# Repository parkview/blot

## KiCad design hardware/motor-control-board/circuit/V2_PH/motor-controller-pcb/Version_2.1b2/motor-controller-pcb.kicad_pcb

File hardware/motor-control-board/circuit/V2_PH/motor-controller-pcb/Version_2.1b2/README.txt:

Project Name:  Blot Motor Controller Board
Project date:  2024-01-21

In Shenzhen Leo and I discussed trying out a new version of the Blot controller PCB that uses normal USB-C (non-PD) with a boost circuit to generate the required 9V to run the two stepper motors.  This is my go at it.

Ideally it would all operate from one USB connector if the current is low enough.

PCB Versions:
-------------

Version 2.2b1:
Production:  JLCPCB, 1.6mm, 4 Layer, Green
Date: TBD

* create a dedicated ESP32-C3-WROOM (Mini?) version.  Gives more GPIO and less soldering

Version 2.1b2:
Production:  JLCPCB, 1.6mm, 4 Layer, Green
Date: TBD

* are R9/R17 (motor decay rate) really needed? If Open, it's set to 16uSec Smart Tune
* test out laser cut plastic solder paste stencil
Done: Fix L2 inductor footprint.  Needs to be bigger?
Done: move L2 1mm away from U3
Done: purchase correct 1A polyfuse
Done: purchase backup 1.5A and 2A + 2.5A 0805 polyfuses
Done: was PWM Vref ok to work with?  Yes and cheapest option.
Done: was DAC Vref ok to work with? (increase 3v3 trace width).  Removed. PWM ok.
Done: delete Vref Pots if not needed, otherwise just use 1 Pot to feed both from 3V3
Done: measure power draw: 5V @ 1.1A for two small motors at 9V.
Done: could add a Fuse LED to indicate when it's activated
Done: could add a programmable LED on A3.  It looks to be available
Done: write pinout data on backside of PCB
Done: change R12 to 33K to allow up to 1.4A output at 9V
Done: Add a XC6227 LDO, to power MCU module when running from 2nd USB connector!
Done: add a 22uF to the Servo power line
Done: swap Blot_PCB_Back_v2.1b1out B5819W (1A) dioes for SS24 (2A)
Done: purchase correct 100uF Caps
Done: change M1 from DVDD to 3V3
Done: on backside, label Motor outputs:  A1/A2, B1/B2
Done: add 3V3, both USB 5V inputs as testpoints and label
Done: connect nSleep to 3V3 instead of DVDD
Done: fix R4/R5 labels
No: could add a Fault LED (pullup to 3V3). Space?

Version 2.1b1:
Production:  JLCPCB, 1.6mm, 4 Layer, Green, 5 PCBs
Date: 2024-02-20

* Initial version.

0  IO2 PWM Dac
1  IO3 Motor Enable
2  IO4
3  IO5
4  IO6
5  IO7
6  IO21
7  IO20
8  IO8
9  IO9
10 IO10
11 3V3
12 GND
13 5V

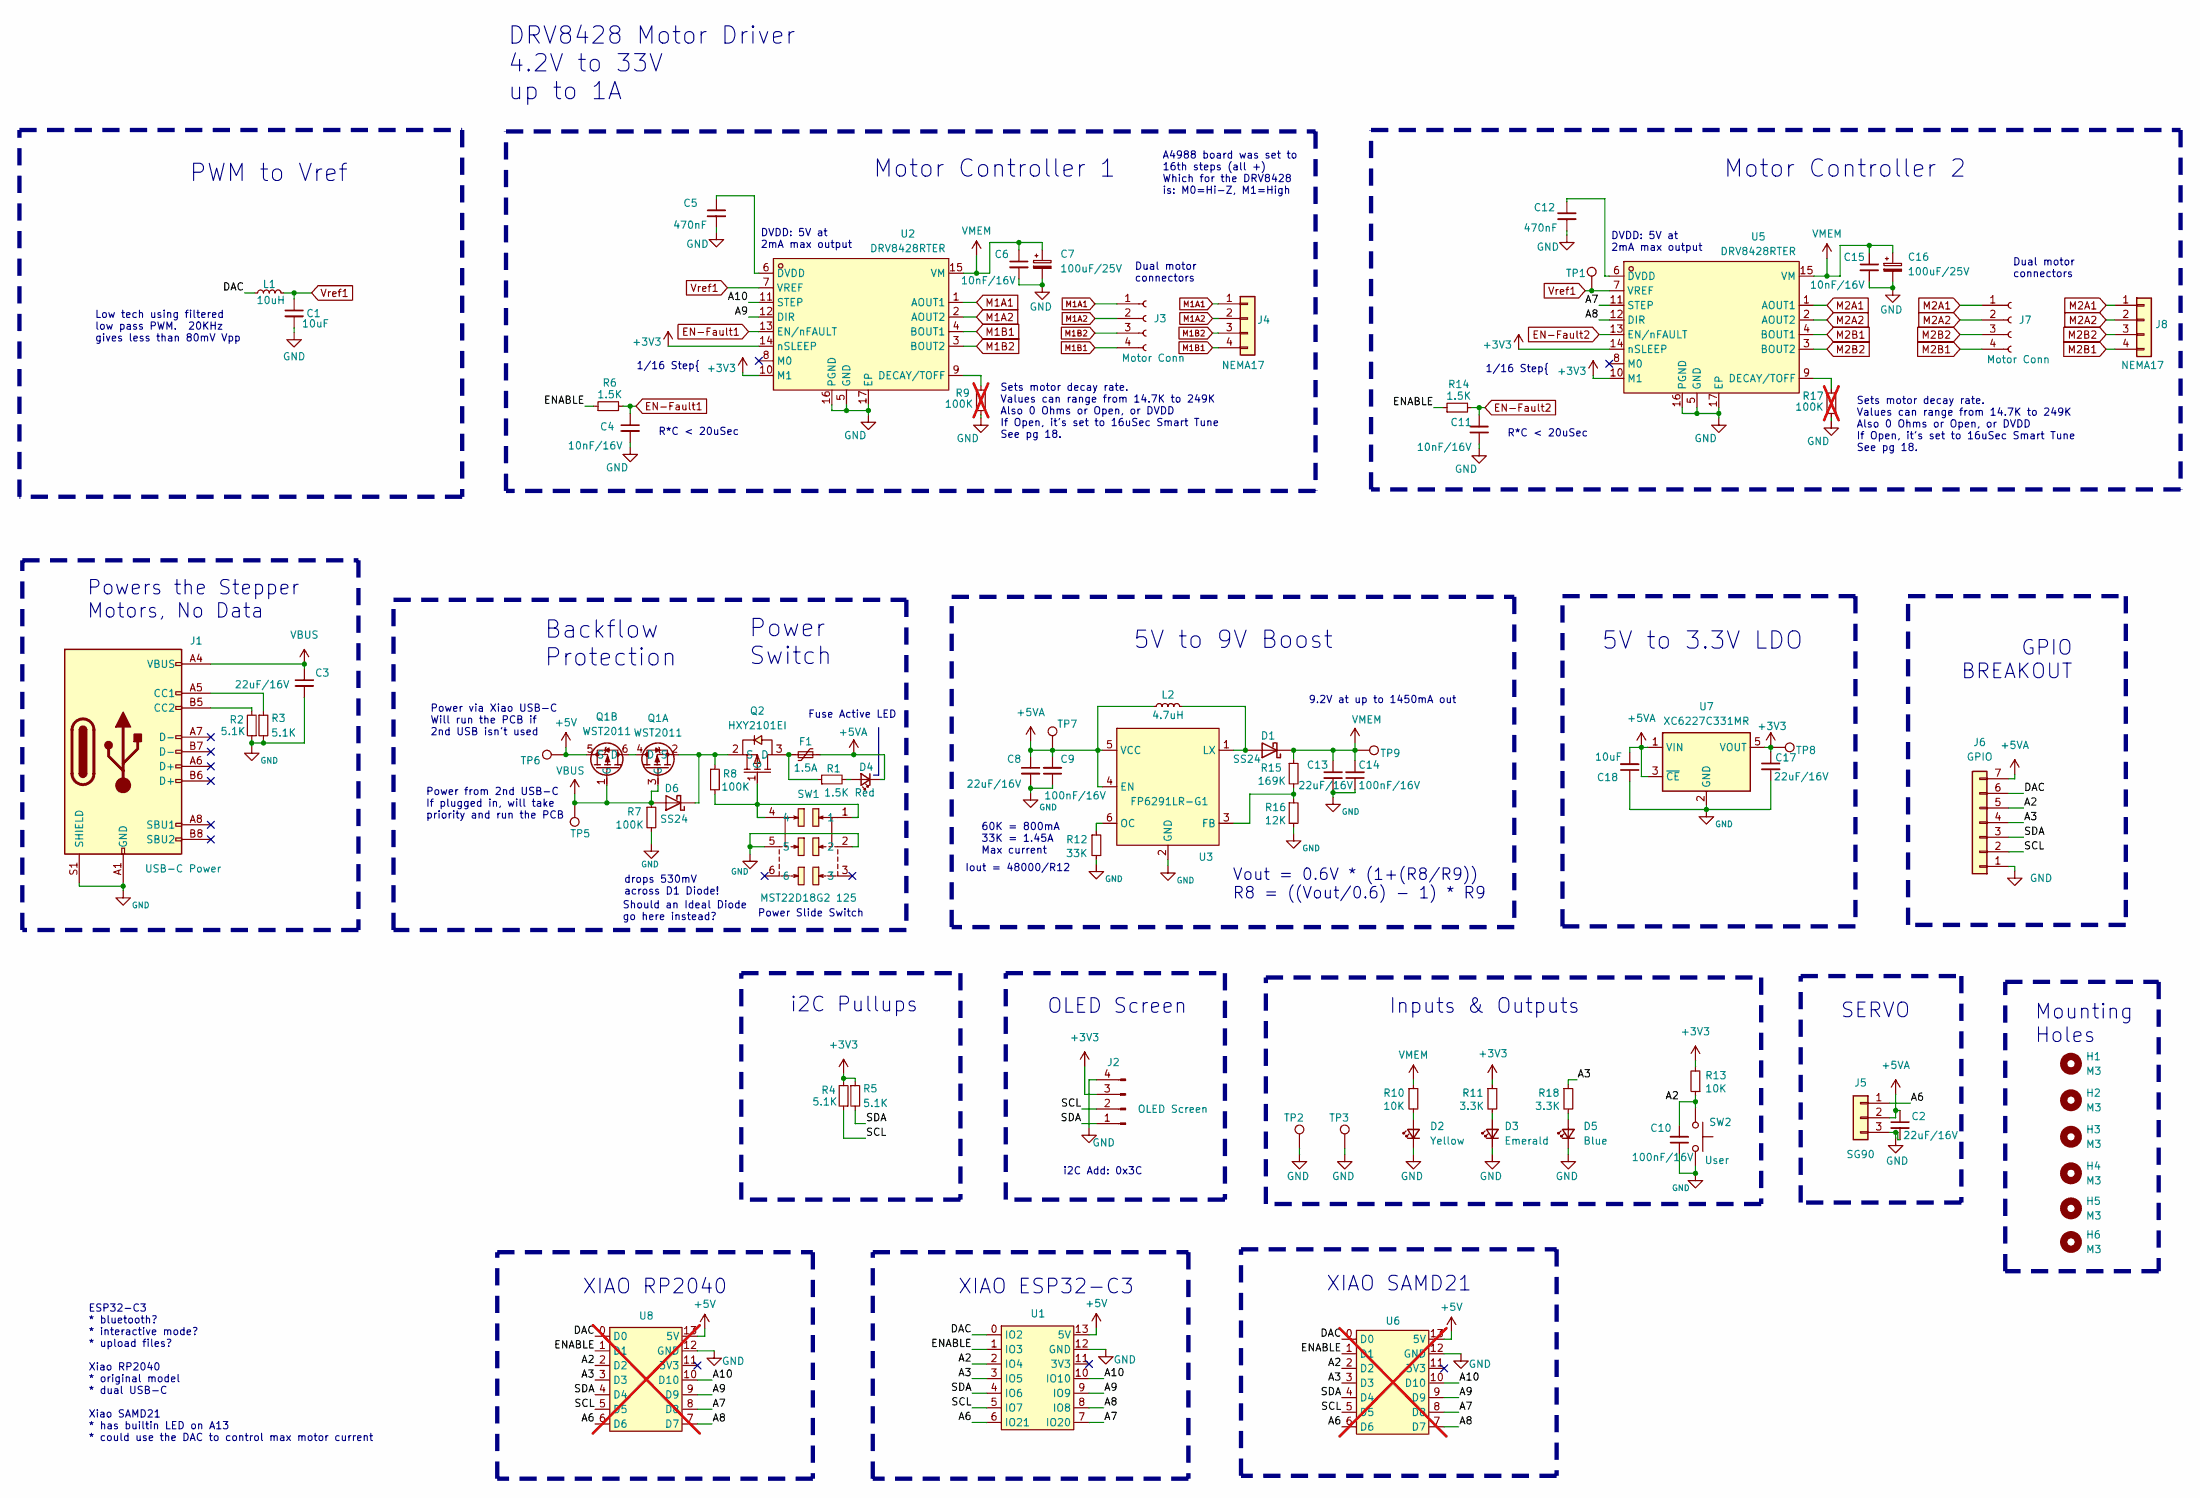
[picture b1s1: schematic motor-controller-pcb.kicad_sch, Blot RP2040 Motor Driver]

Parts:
C1, C18: 10uF; C_0603_1608Metric; JLC Part 50V
C2, C3, C8, C13, C17: 22uF/16V; C_0603_1608Metric; LCSC C6119868
C4, C6, C11, C15: 10nF/16V; C_0603_1608Metric; LCSC C519406
C5, C12: 470nF; C_0603_1608Metric; LCSC C106851
C7, C16: 100uF/25V; CAP-SMD_BD6.3-L6.6-W6.6-LS7.3-FD; LCSC C4747964
C9, C10, C14: 100nF/16V; C_0603_1608Metric; LCSC C30926
D1, D6: SS24; D_SMA; LCSC C466490
D2: Yellow; LED_0603_1608Metric; LCSC C965802
D3: Emerald; LED_0603_1608Metric; LCSC C965804
D4: Red; LED_0603_1608Metric; LCSC C965799
D5: Blue; LED_0603_1608Metric; LCSC C965807
F1: 1.5A; Fuse_0805_2012Metric; LCSC C269104
H1, H2, H3, H4, H5, H6: M3; MountingHole_3.2mm_M3; LCSC X
J1: USB-C Power; USB_C_Receptacle_HRO_TYPE-C-31-M-12; LCSC C2765186
J2: OLED Screen; PinSocket_1x04_P2.54mm_Vertical; LCSC C2691448
J3, J7: Motor Conn; CONN-SMD_4P-P1.25_533980471; LCSC C2845390
J4, J8: NEMA17; PinSocket_1x04_P2.54mm_Vertical; LCSC C2845390
J5: SG90; PinSocket_1x03_P2.54mm_Vertical; LCSC C2937625
J6: GPIO; PinSocket_1x07_P2.54mm_Vertical; LCSC X
L1: 10uH; L_0603_1608Metric; LCSC C51942
L2: 4.7uH; IND-SMD_L4.4-W4.2; LCSC C5159366
Q1: WST2011; SOT-23-6_L2.9-W1.6-P0.95-LS2.8-BR; LCSC Part C148368
Q2: HXY2101EI; SOT-323-3_L2.1-W1.3-P1.30-LS2.3-BL; LCSC Part C5148643
R1, R6, R14: 1.5K; R_0603_1608Metric; LCSC C22843
R2, R3, R4, R5: 5.1K; R_0603_1608Metric; LCSC C23186
R7, R8: 100K; R_0603_1608Metric; LCSC C14675
R9, R17: 100K; R_0603_1608Metric; LCSC C14675; not fitted
R10, R13: 10K; R_0603_1608Metric; LCSC C98220
R11, R18: 3.3K; R_0603_1608Metric; LCSC C114612
R12: 33K; R_0603_1608Metric; LCSC C4216
R15: 169K; R_0603_1608Metric; LCSC C137791
R16: 12K; R_0603_1608Metric; LCSC C22790
SW1: MST22D18G2 125; SW-SMD_MST22D18G2; LCSC Part C2906280
SW2: User; SW_SMD_SPST_5x3; LCSC C843665
TP1, TP2, TP3, TP5, TP6, TP7, TP8, TP9: TestPoint; TestPoint_THTPad_1.0x1.0mm_Drill0.5mm; LCSC X
U1: QTPYXIAORP2040; LCSC X
U2, U5: DRV8428RTER; WQFN-16_L3.0-W3.0-P0.50-BL-EP1.7; LCSC Part C2857955
U3: FP6291LR-G1; SOT-23-6_L2.9-W1.6-P0.95-LS2.8-BR; LCSC Part C18701
U6, U8: QTPYXIAORP2040; LCSC X; not fitted
U7: XC6227C331MR; SOT-23-5; LCSC C216640

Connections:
+3V3: C17.1, J2.3, R4.2, R5.1, R11.1, R13.2, TP8.1, U2.10 (M1), U2.14 (nSLEEP), U5.10 (M1), U5.14 (nSLEEP), U7.5 (VOUT)
+5V: Q1.5 (S), TP6.1, U1.13 (5V), U6.13 (5V), U8.13 (5V)
+5VA: C2.1, C8.1, C9.2, C18.2, D4.1 (K), F1.2, J5.2, J6.7, L2.1, TP7.1, U3.4 (EN), U3.5 (VCC), U7.1 (VIN), U7.3 (~CE)
/A2: C10.2, J6.5, R13.1, SW2.1, U1.2 (IO4), U6.2 (D2), U8.2 (D2)
/A3: J6.4, R18.1, U1.3 (IO5), U6.3 (D3), U8.3 (D3)
/A6: J5.1, U1.6 (IO21), U6.6 (D6), U8.6 (D6)
/A7: U1.7 (IO20), U5.11 (STEP), U6.8 (D8), U8.8 (D8)
/A8: U1.8 (IO8), U5.12 (DIR), U6.7 (D7), U8.7 (D7)
/A9: U1.9 (IO9), U2.12 (DIR), U6.9 (D9), U8.9 (D9)
/A10: U1.10 (IO10), U2.11 (STEP), U6.10 (D10), U8.10 (D10)
/DAC: J6.6, L1.1, U1.0 (IO2), U6.0 (D0), U8.0 (D0)
/ENABLE: R6.1, R14.1, U1.1 (IO3), U6.1 (D1), U8.1 (D1)
/SCL: J2.2, J6.2, R4.1, U1.5 (IO7), U6.5 (D5), U8.5 (D5)
/SDA: J2.1, J6.3, R5.2, U1.4 (IO6), U6.4 (D4), U8.4 (D4)
EN-Fault1: C4.1, R6.2, U2.13 (EN/nFAULT)
EN-Fault2: C11.1, R14.2, U5.13 (EN/nFAULT)
GND: C1.2, C2.2, C3.2, C4.2, C5.2, C6.2, C7.2, C8.2, C9.1, C10.1, C11.2, C12.2, C13.2, C14.1, C15.2, C16.2, C17.2, C18.1, D2.1 (K), D3.1 (K), D5.1 (K), J1.A1 (GND), J1.A12 (GND), J1.B1 (GND), J1.B12 (GND), J1.S1 (SHIELD), J2.4, J5.3, J6.1, R2.1, R3.2, R7.2, R9.1, R12.2, R16.2, R17.1, SW1.2, SW1.5, SW2.2, TP2.1, TP3.1, U1.12 (GND), U2.5 (GND), U2.16 (PGND), U2.17 (EP), U3.2 (GND), U5.5 (GND), U5.16 (PGND), U5.17 (EP), U6.12 (GND), U7.2 (GND), U8.12 (GND)
M1A1: J3.1, J4.1, U2.1 (AOUT1)
M1A2: J3.2, J4.2, U2.2 (AOUT2)
M1B1: J3.4, J4.4, U2.4 (BOUT1)
M1B2: J3.3, J4.3, U2.3 (BOUT2)
M2A1: J7.1, J8.1, U5.1 (AOUT1)
M2A2: J7.2, J8.2, U5.2 (AOUT2)
M2B1: J7.4, J8.4, U5.4 (BOUT1)
M2B2: J7.3, J8.3, U5.3 (BOUT2)
unnamed: D1.2 (A), L2.2, U3.1 (LX)
unnamed: D2.2 (A), R10.2
unnamed: D3.2 (A), R11.2
unnamed: D4.2 (A), R1.2
unnamed: D5.2 (A), R18.2
unnamed: D6.1 (K), Q1.2 (S), Q2.2 (S), R8.1
unnamed: J1.A5 (CC1), R3.1
unnamed: J1.B5 (CC2), R2.2
unnamed: Q1.4 (D), Q1.6 (D)
unnamed: F1.1, Q2.3 (D), R1.1
unnamed: Q2.1 (G), R8.2, SW1.1, SW1.4
unnamed: R9.2, U2.9 (DECAY/TOFF)
unnamed: C5.1, U2.6 (DVDD)
unnamed: R15.2, R16.1, U3.3 (FB)
unnamed: R12.1, U3.6 (OC)
unnamed: R17.2, U5.9 (DECAY/TOFF)
unnamed: C12.1, U5.6 (DVDD)
VBUS: C3.1, D6.2 (A), J1.A4 (VBUS), J1.A9 (VBUS), J1.B4 (VBUS), J1.B9 (VBUS), Q1.1 (G), Q1.3 (G), R7.1, TP5.1
VMEM: C6.1, C7.1, C13.1, C14.2, C15.1, C16.1, D1.1 (K), R10.1, R15.1, TP9.1, U2.15 (VM), U5.15 (VM)
Vref1: C1.1, L1.2, TP1.1, U2.7 (VREF), U5.7 (VREF)

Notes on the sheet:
XIAO ESP32-C3
Inputs & Outputs
5V to 9V Boost
GPIO BREAKOUT
Power via Xiao USB-C Will run the PCB if 2nd USB isn't used
Backflow Protection
DRV8428 Motor Driver 4.2V to 33V up to 1A
PWM to Vref
Fuse Active LED
R*C < 20uSec
Mounting Holes
Dual motor connectors
DVDD: 5V at 2mA max output
Power from 2nd USB-C If plugged in, will take priority and run the PCB
Power Switch
Power Slide Switch
XIAO RP2040
Sets motor decay rate. Values can range from 14.7K to 249K Also 0 Ohms or Open, or DVDD If Open, it's set to 16uSec Smart Tune See pg 18.
OLED Screen
i2C Pullups
Iout = 48000/R12
Motor Controller 2
Low tech using filtered low pass PWM. 20KHz gives less than 80mV Vpp
XIAO SAMD21
9.2V at up to 1450mA out
Powers the Stepper Motors, No Data
5V to 3.3V LDO
1/16 Step{
ESP32-C3 * bluetooth? * interactive mode? * upload files? Xiao RP2040 * original model * dual USB-C Xiao SAMD21 * has builtin LED on A13 * could use the DAC to control max motor current
SERVO
A4988 board was set to 16th steps (all +) Which for the DRV8428 is: M0=Hi-Z, M1=High
Motor Controller 1
Should an Ideal Diode go here instead?
i2C Add: 0x3C
drops 530mV across D1 Diode!
60K = 800mA 33K = 1.45A Max current
Vout = 0.6V * (1+(R8/R9)) R8 = ((Vout/0.6) - 1) * R9

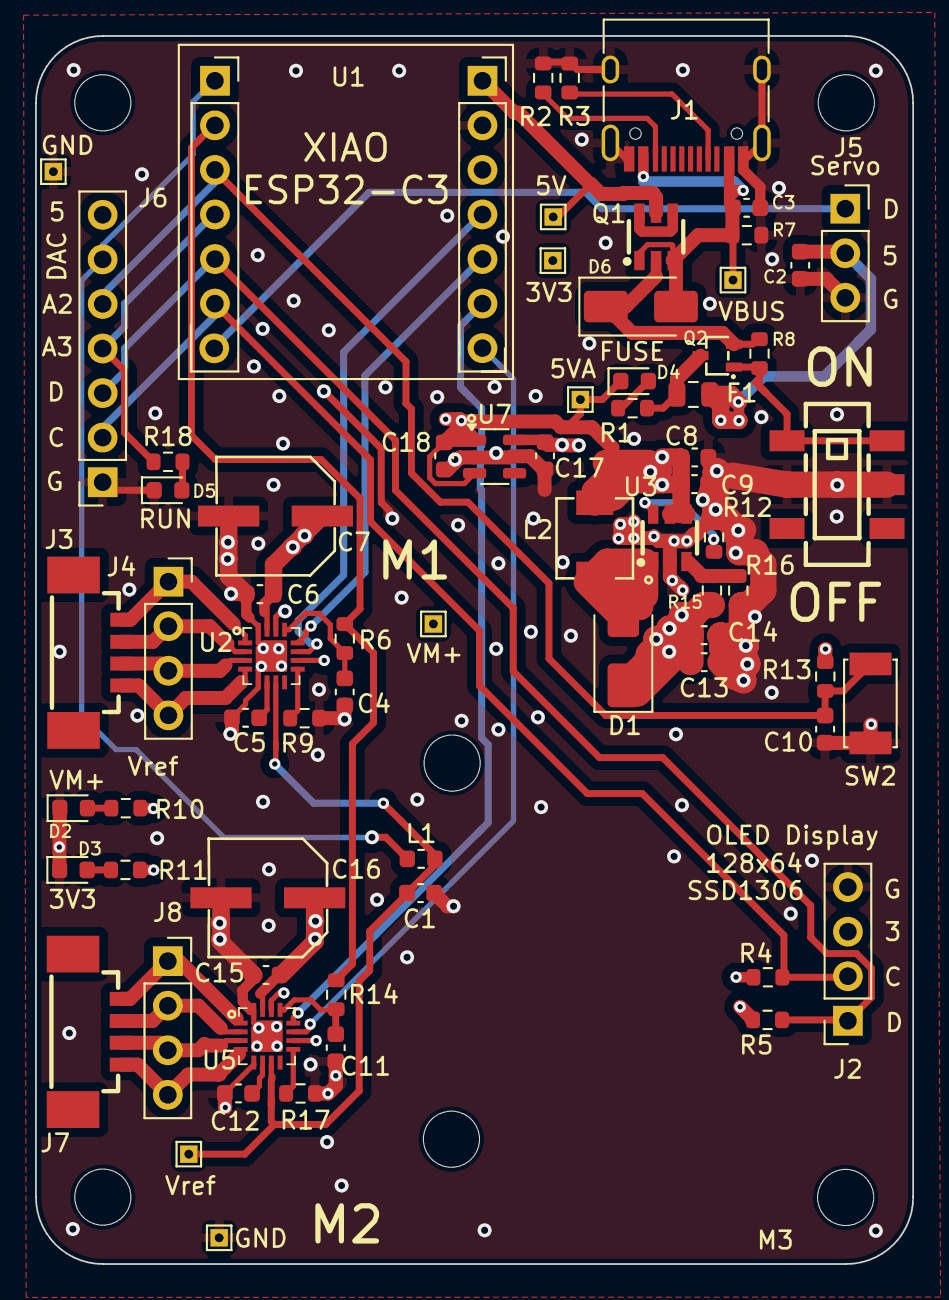
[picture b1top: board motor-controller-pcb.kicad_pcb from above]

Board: 4 copper layers, 50.0 x 70.0 mm, 76 parts (0 on the bottom side), 45 nets.

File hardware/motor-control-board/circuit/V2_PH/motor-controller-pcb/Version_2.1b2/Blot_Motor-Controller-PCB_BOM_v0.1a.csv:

"Reference","Value","Footprint","DNP","Description","LCSC","LCSC Part","Qty"
"C1","10uF","Capacitor_SMD:C_0603_1608Metric","","16V","C14663","","1"
"C2","100nF","Capacitor_SMD:C_0603_1608Metric","","16V","C14663","","1"
"C3, C8, C13","22uF/16V","Capacitor_SMD:C_0603_1608Metric","","","C6119868","","3"
"C4, C6, C11, C15","10nF/16V","Capacitor_SMD:C_0603_1608Metric","","","C519406","","4"
"C5, C12","470nF","Capacitor_SMD:C_0603_1608Metric","","","C106851","","2"
"C7, C16","100uF/25V","blot-footprints:CAP-SMD_BD6.3-L6.6-W6.6-LS7.3-FD","","","C4747964","","2"
"C9, C10, C14","100nF/16V","Capacitor_SMD:C_0603_1608Metric","","","C30926","","3"
"D1, D4","B5819W","Diode_SMD:D_SOD-123","","","C2943878","","2"
"D2","Orange","LED_SMD:LED_0603_1608Metric","","","C965800","","1"
"D3","Emerald","LED_SMD:LED_0603_1608Metric","","","C965804","","1"
"F1","1A","Fuse:Fuse_0805_2012Metric","","","C269104","","1"
"FB1","150","Inductor_SMD:L_1206_3216Metric","","","C5297452","","1"
"H1-H6","M3","MountingHole:MountingHole_3.2mm_M3","","","X","","6"
"J1","USB-C Power","Connector_USB:USB_C_Receptacle_HRO_TYPE-C-31-M-12","","","C2765186","","1"
"J2","OLED Screen","Connector_PinSocket_2.54mm:PinSocket_1x04_P2.54mm_Vertical","","","C2691448","","1"
"J3, J7","Motor Conn","blot-footprints:CONN-SMD_4P-P1.25_533980471","","","C2845390","","2"
"J4, J8","NEMA17","Connector_PinSocket_2.54mm:PinSocket_1x04_P2.54mm_Vertical","","","C2845390","","2"
"J5","SG90","Connector_PinSocket_2.54mm:PinSocket_1x03_P2.54mm_Vertical","","","C2937625","","1"
"J6","GPIO","Connector_PinSocket_2.54mm:PinSocket_1x07_P2.54mm_Vertical","","","","","1"
"JP1, JP2","Jumper_2_Open","blot-footprints:JUMPER-2Psml_UnBridged_RoundedPad2x1mm","","","","","2"
"JP3, JP4","Jumper_3_Bridged12","blot-footprints:JUMPER-3Psml_Bridged_RoundedPad2x1mm","","","X","","2"
"L1","2.2uH","Inductor_SMD:L_0603_1608Metric","","","C5339202","","1"
"L2","4.7uH","blot-footprints:L1008","","","C5159366","","1"
"Q1","WST2011","blot-footprints:SOT-23-6_L2.9-W1.6-P0.95-LS2.8-BR","","","C148368","C148368","1"
"Q2","HXY2101EI","blot-footprints:SOT-323-3_L2.1-W1.3-P1.30-LS2.3-BL","","","C5148643","C5148643","1"
"R1","16R","Resistor_SMD:R_0603_1608Metric","","","C22843","","1"
"R2-R5","5.1K","Resistor_SMD:R_0603_1608Metric","","","C23186","","4"
"R6, R14","1.5K","Resistor_SMD:R_0603_1608Metric","","","C22843","","2"
"R7-R9, R17","100K","Resistor_SMD:R_0603_1608Metric","","","C14675","","4"
"R10, R13","10K","Resistor_SMD:R_0603_1608Metric","","","C98220","","2"
"R11","2.7K","Resistor_SMD:R_0603_1608Metric","","","C114612","","1"
"R12","60.4K","Resistor_SMD:R_0603_1608Metric","","","C23089","","1"
"R15","169K","Resistor_SMD:R_0603_1608Metric","","","C137791","","1"
"R16","12K","Resistor_SMD:R_0603_1608Metric","","","C22790","","1"
"RV1, RV2","30K","blot-footprints:RES-ADJ-SMD_3P-L3.0-W3.8-P1.75-BR","","","C6331330","","2"
"SW1","MST22D18G2 125","blot-footprints:SW-SMD_MST22D18G2","","","C2906280","C2906280","1"
"SW2","User","blot-footprints:SW_SMD_SPST_5x3","","","C843665","","1"
"TP1-TP4","TestPoint","TestPoint:TestPoint_THTPad_1.0x1.0mm_Drill0.5mm","","","X","","4"
"U1","DAC5571IDBVR","easyeda2kicad:SOT-23-6_L2.9-W1.6-P0.95-LS2.8-BR","","","C24061","C24061","1"
"U2, U5","DRV8428RTER","blot-footprints:WQFN-16_L3.0-W3.0-P0.50-BL-EP1.7","","","C2857955","C2857955","2"
"U3","FP6291LR-G1","blot-footprints:SOT-23-6_L2.9-W1.6-P0.95-LS2.8-BR","","","C18701","C18701","1"
"U4","RP2040 XIAO","blot-footprints:QTPYXIAORP2040","","","X","","1"

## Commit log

2024-02-13 adding initial V2-beta schematic and PCB layout
2024-02-13 PCB ready for manufacture
2024-02-13 adding PCB schematic PDF
2024-02-13 updated components with LCSC part numbers
2024-02-13 updated schematic PDF and added more datasheet
2024-02-19 adding in new PWM/DAC design
2024-03-02 cleaned up Silkscreen errors
2024-03-24 adding in new Blot PVB version v2.1b2
2024-03-24 adding in schematic
